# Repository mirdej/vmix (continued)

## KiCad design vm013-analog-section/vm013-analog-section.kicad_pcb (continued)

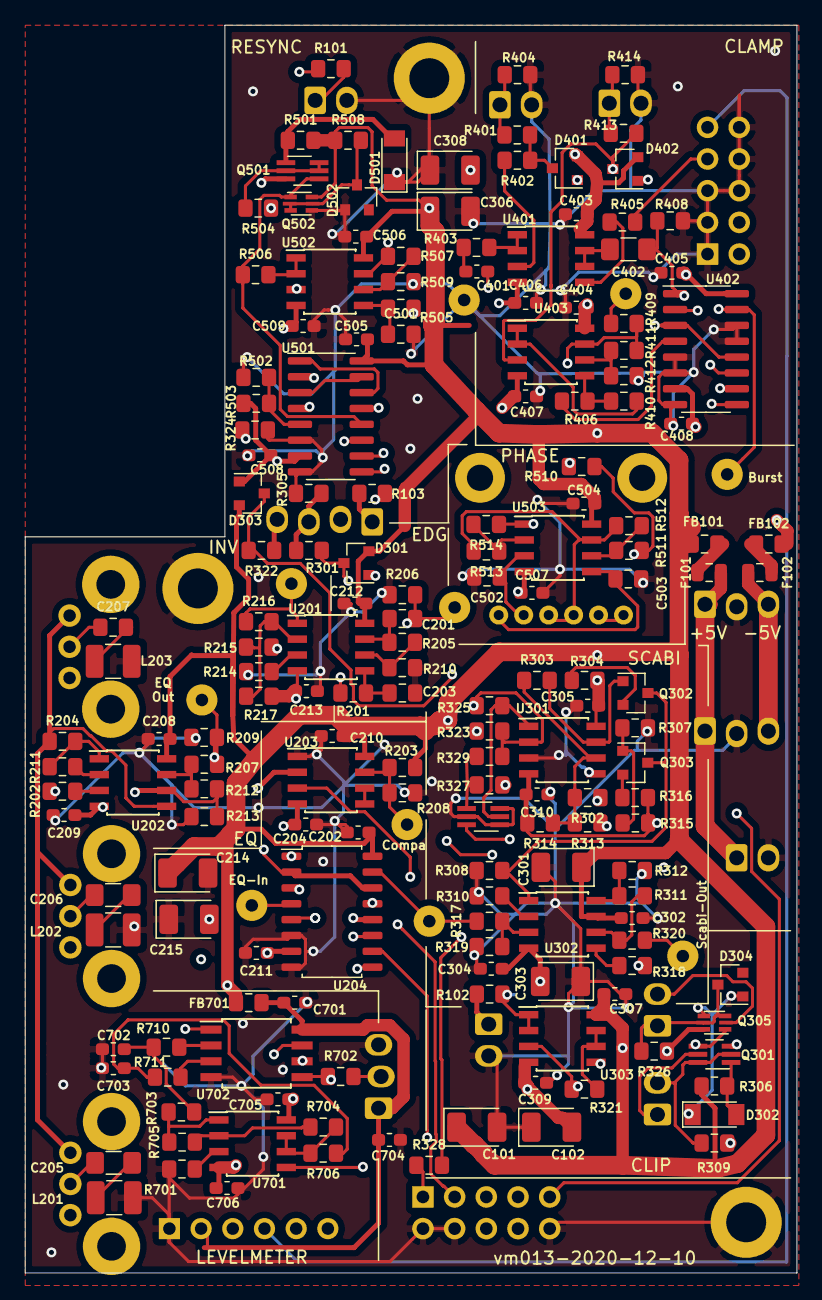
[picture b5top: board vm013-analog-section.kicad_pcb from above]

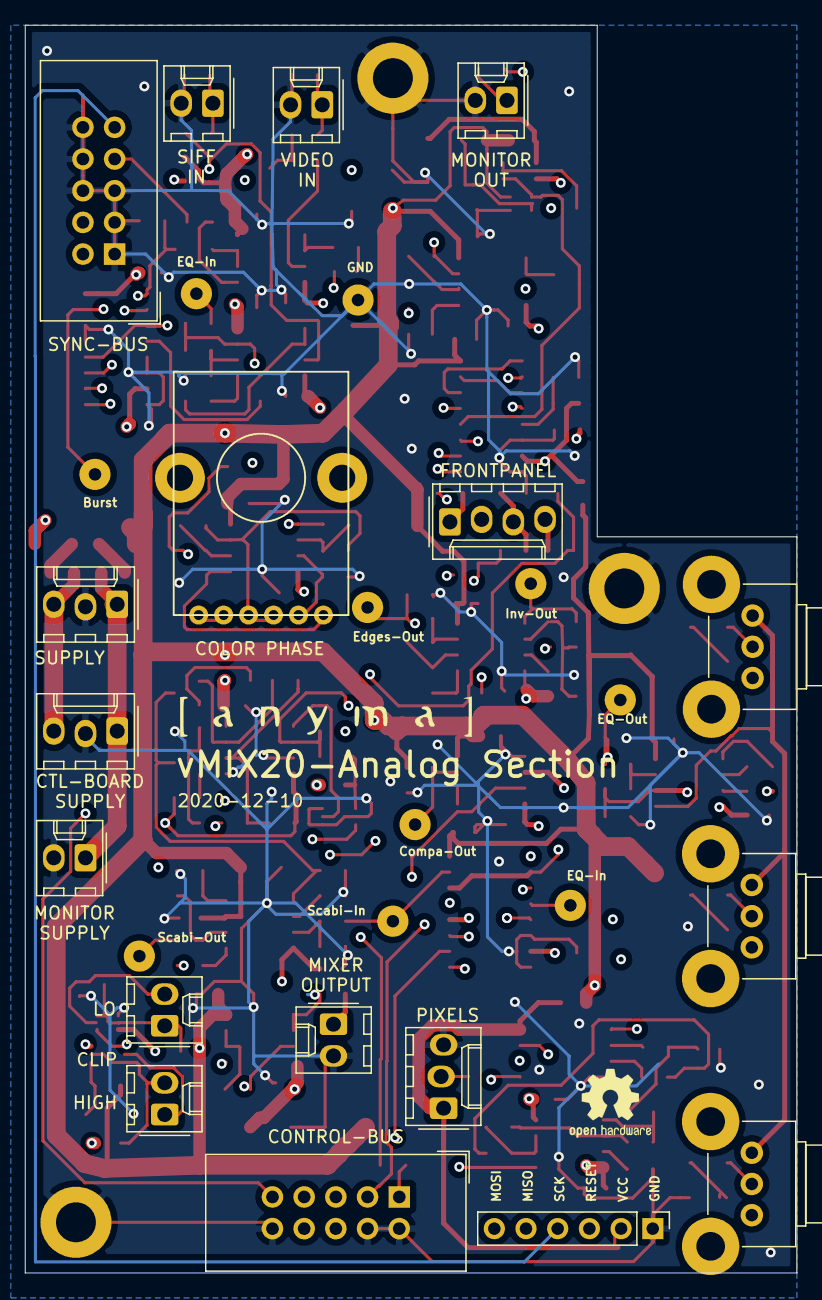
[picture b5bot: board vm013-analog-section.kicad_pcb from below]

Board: 4 copper layers, 61.8 x 100.0 mm, 205 parts (20 on the bottom side), 124 nets.

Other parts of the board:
H601, H602, H603: MountingHole_Pad; MountingHole_3.2mm_M3_ISO7380_Pad
U601: LOGO; logo_anyma
U602: LOGO; OSHW-Logo2_7.3x6mm_SilkScreen

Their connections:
GND: H601.1, H602.1, H603.1; also elsewhere on the board

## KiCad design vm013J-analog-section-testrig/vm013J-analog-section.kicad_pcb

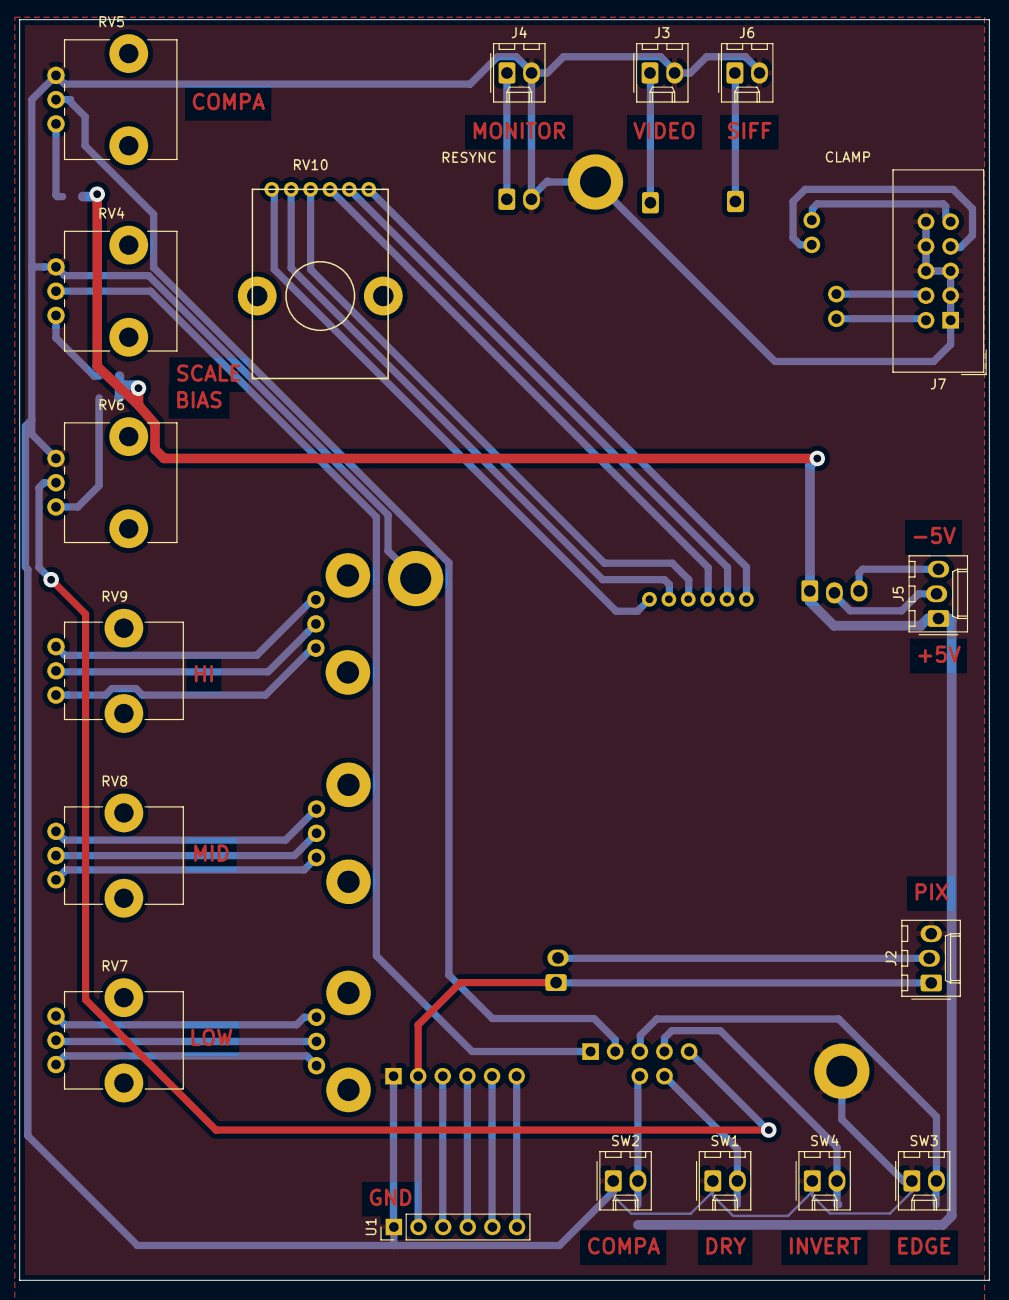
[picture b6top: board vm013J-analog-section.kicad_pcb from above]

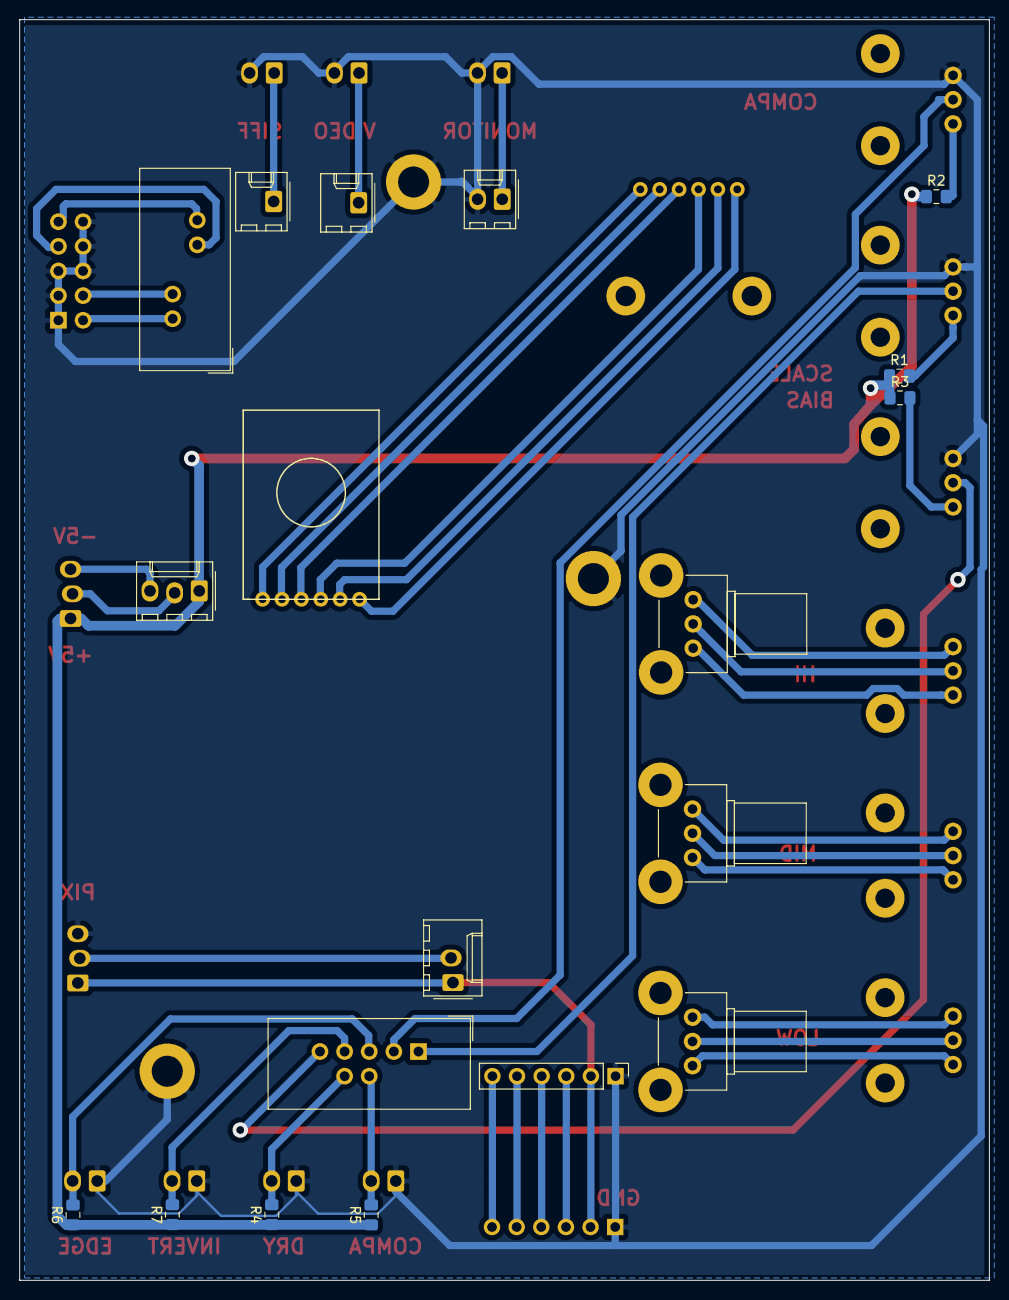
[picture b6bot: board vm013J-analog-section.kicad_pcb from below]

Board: 4 copper layers, 100.0 x 130.0 mm, 40 parts (19 on the bottom side), 42 nets.

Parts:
H601, H602, H603: MountingHole_Pad; MountingHole_3.2mm_M3_ISO7380_Pad
J1, J2: pixels; Molex_KK-254_AE-6410-03A_1x03_P2.54mm_Vertical
J3, J103: COMPOSITE-INPUT; Molex_KK-254_AE-6410-02A_1x02_P2.54mm_Vertical
J4, J104: MONITOR_OUT; Molex_KK-254_AE-6410-02A_1x02_P2.54mm_Vertical
J5, J105: Power; Molex_KK-254_AE-6410-03A_1x03_P2.54mm_Vertical
J6, J106: SIFF-INPUT; Molex_KK-254_AE-6410-02A_1x02_P2.54mm_Vertical
J7, J110: SYNC-BUS; IDC-Header_2x05_P2.54mm_Vertical
J107: FROM CTL; IDC-Header_2x05_P2.54mm_Vertical
R1, R2, R3: 40k; R_0805_2012Metric_Pad1.15x1.40mm_HandSolder
R4, R5, R6, R7: 4k7; R_0805_2012Metric_Pad1.15x1.40mm_HandSolder
RV1, RV2, RV3: R_POT; Potentiometer_Alps_RK09K_Single_Horizontal
RV4, RV5, RV6: R_POT; Potentiometer_Alps_RK09L_Single_Vertical
RV7, RV8, RV9: R_POT; Potentiometer_Alps_RK09K_Single_Vertical
RV10, RV501: R_POT_Dual; RK12L123
SW1, SW2, SW3, SW4: SW_Push; Molex_KK-254_AE-6410-02A_1x02_P2.54mm_Vertical
U1, U7: AnymaISP; PinHeader_1x06_P2.54mm_Vertical

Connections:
+5V: J5.1, J105.1, R1.1, R2.1, R3.1, R4.1, R5.1, R6.1, R7.1
/Levelmeter/miso: U1.5, U7.5
/Levelmeter/mosi: U1.6, U7.6
/Levelmeter/reset: U1.3, U7.3
/Levelmeter/sck: U1.4, U7.4
GND: H601.1, H602.1, H603.1, J2.3, J3.2, J4.2, J6.2, J7.1, J7.3, J7.5, J7.6, J7.8, J7.10, J104.2, RV4.3, RV5.3, RV6.3, SW1.1, SW2.1, SW3.1, SW4.1, U1.1, U7.1
unnamed: J1.2, J2.2
unnamed: J3.1, J103.1
unnamed: J4.1, J104.1
unnamed: J5.2, J105.2
unnamed: J5.3, J105.3
unnamed: J6.1, J106.1
unnamed: R1.2, RV4.1
unnamed: R2.2, RV5.1
unnamed: R3.2, RV6.1
unnamed: RV1.1, RV7.1
unnamed: RV1.2, RV7.2
unnamed: RV1.3, RV7.3
unnamed: RV2.1, RV8.1
unnamed: RV2.2, RV8.2
unnamed: RV2.3, RV8.3
unnamed: RV3.1, RV9.1
unnamed: RV3.2, RV9.2
unnamed: RV3.3, RV9.3
unnamed: RV10.1, RV501.1
unnamed: RV10.2, RV501.2
unnamed: RV10.3, RV501.3
unnamed: RV10.4, RV501.4
unnamed: RV10.5, RV501.5
unnamed: RV10.6, RV501.6
VCC: J1.1, J2.1, U1.2, U7.2
bias_cv: J107.9, RV6.2
compa_bypass: J107.6, R5.2, SW2.2
compa_cv: J107.3, RV5.2
drywet: J107.8, R4.2, SW1.2
edges_bypass: J107.5, R6.2, SW3.2
genlock: J7.7, J110.7
hsync: J7.2, J110.2
inverter_bypass: J107.7, R7.2, SW4.2
porch: J7.4, J110.4
scale_cv: J107.1, RV4.2
vsync: J7.9, J110.9

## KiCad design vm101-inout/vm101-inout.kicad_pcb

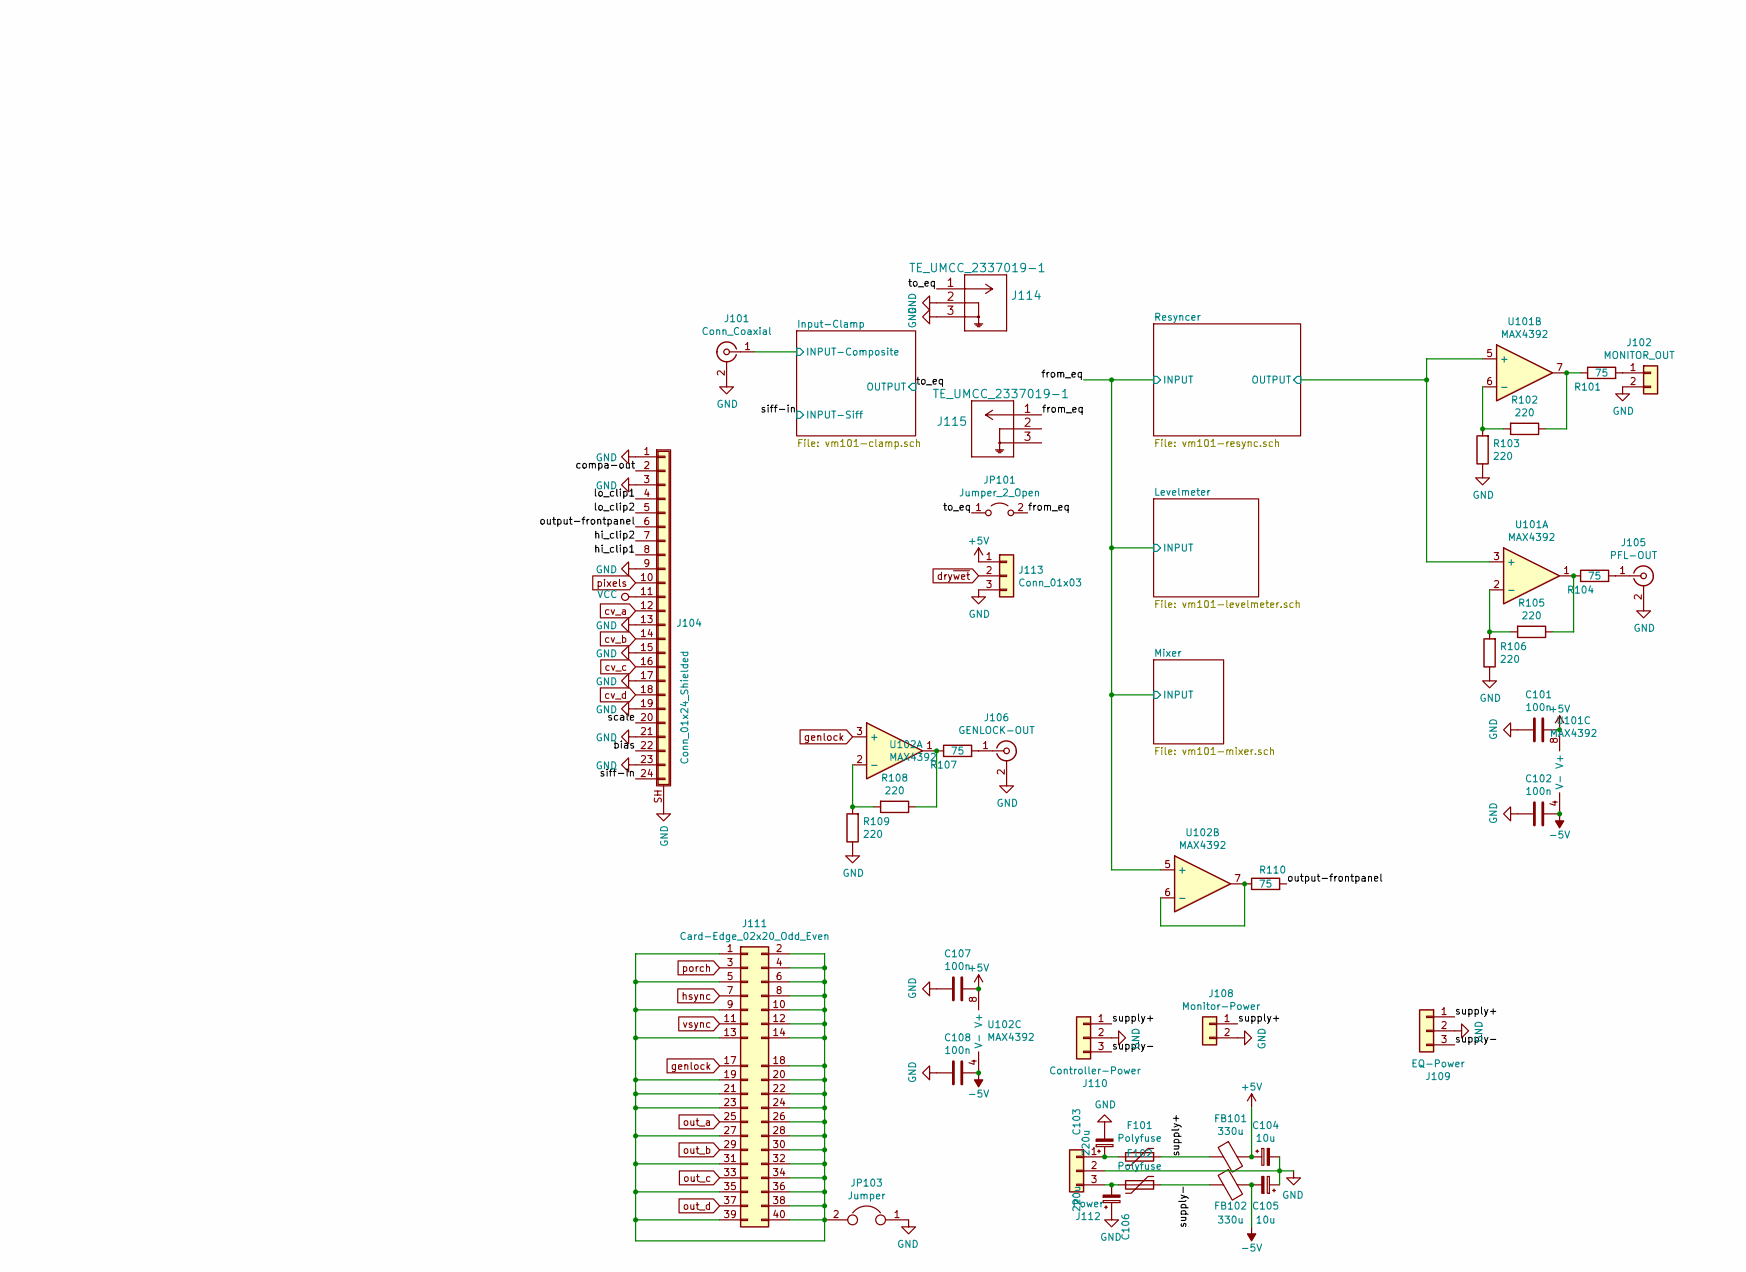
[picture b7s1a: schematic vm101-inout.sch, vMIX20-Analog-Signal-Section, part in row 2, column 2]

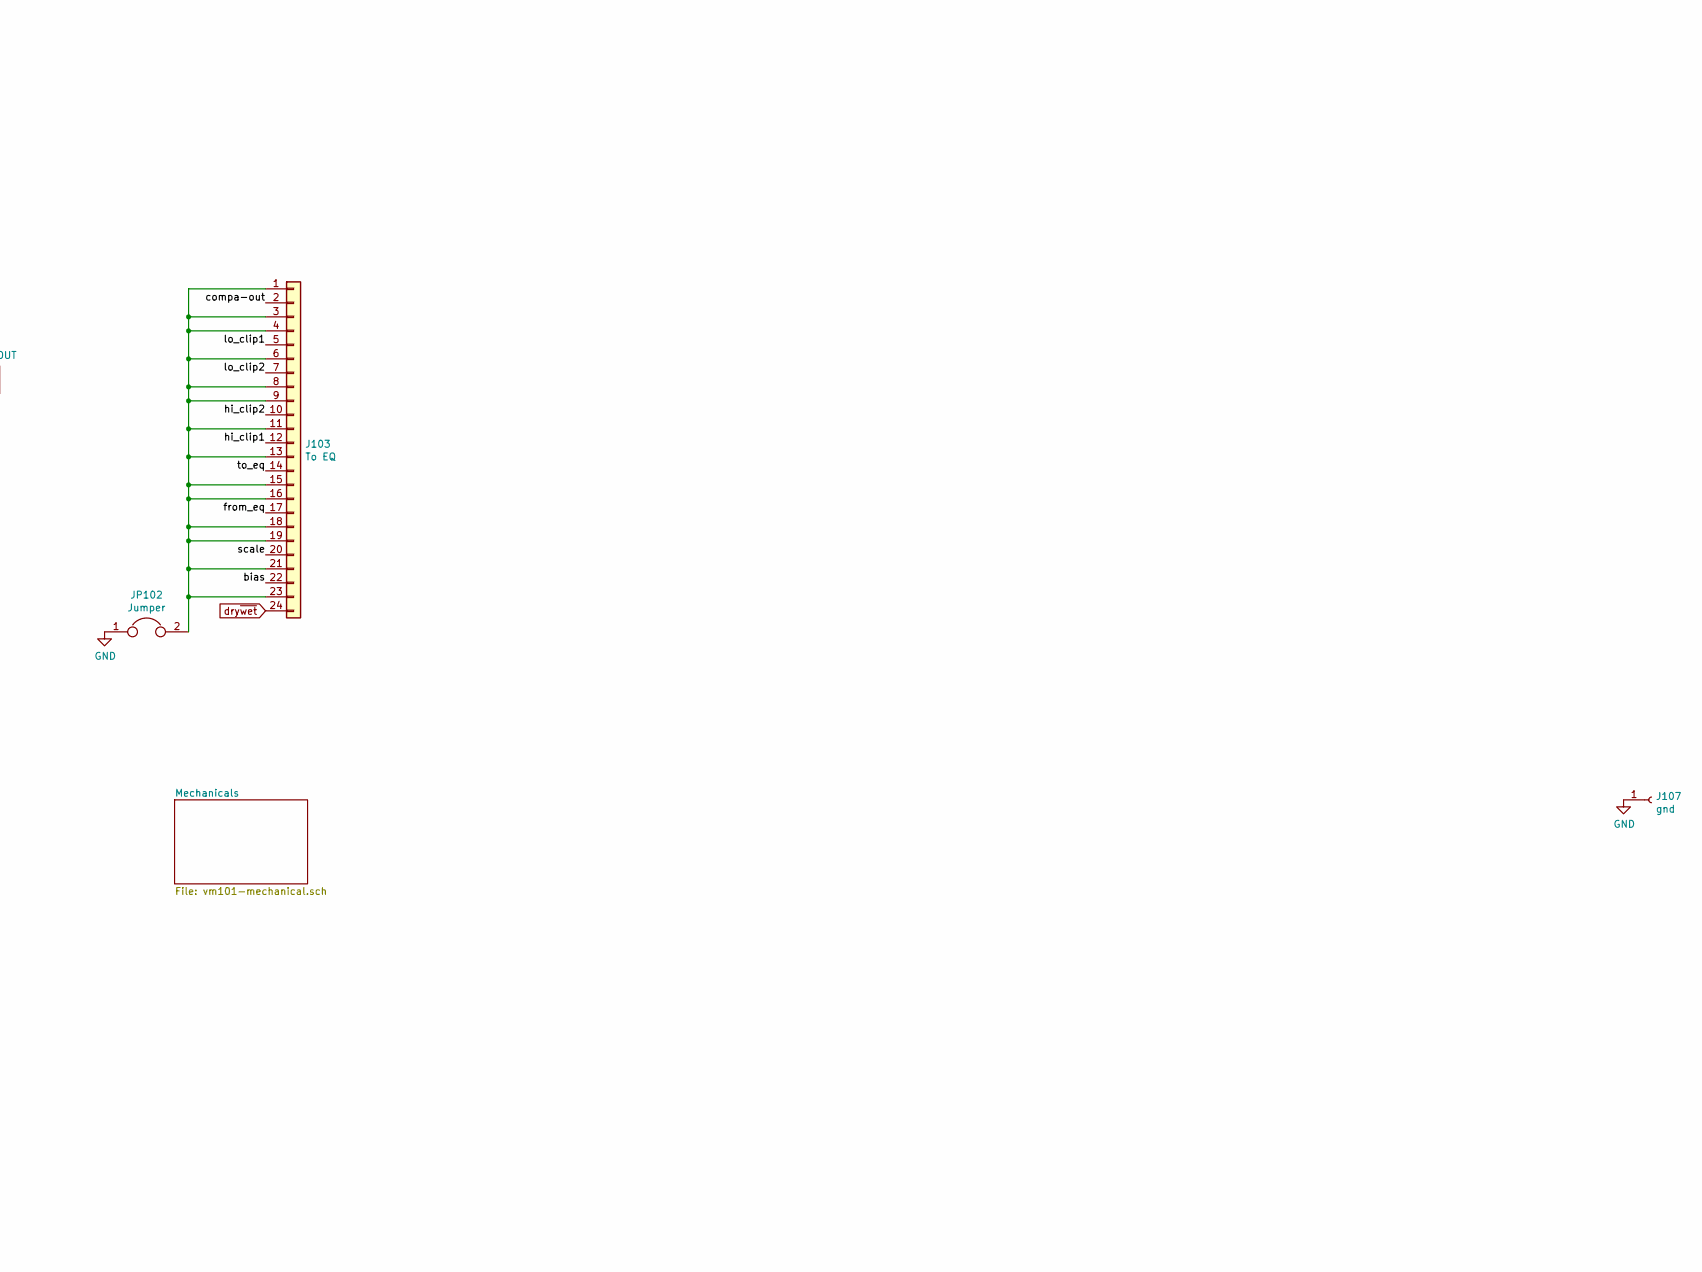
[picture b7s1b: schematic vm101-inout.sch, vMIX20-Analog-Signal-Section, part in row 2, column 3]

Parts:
C101, C102, C107, C108: 100n; C_0603_1608Metric_Pad1.05x0.95mm_HandSolder
C103, C106: 220u; CP_Elec_10x10.5
C104, C105: 10u; CP_EIA-3528-21_Kemet-B_Pad1.50x2.35mm_HandSolder
F101, F102: Polyfuse; Fuse_0805_2012Metric
FB101, FB102: 330u; L_0805_2012Metric_Pad1.15x1.40mm_HandSolder
J101: Conn_Coaxial; BNC_Amphenol_B6252HB-NPP3G-50_Horizontal
J102: MONITOR_OUT; Molex_KK-254_AE-6410-02A_1x02_P2.54mm_Vertical
J103: To EQ; Hirose_FH12-24S-0.5SH_1x24-1MP_P0.50mm_Horizontal
J104: Conn_01x24_Shielded; Hirose_FH12-24S-0.5SH_1x24-1MP_P0.50mm_Horizontal
J105: PFL-OUT; BNC_Amphenol_B6252HB-NPP3G-50_Horizontal
J106: GENLOCK-OUT; BNC_Amphenol_B6252HB-NPP3G-50_Horizontal
J107: gnd; Solderpad_1mm
J108: Monitor-Power; Molex_KK-254_AE-6410-02A_1x02_P2.54mm_Vertical
J109: EQ-Power; Molex_KK-254_AE-6410-03A_1x03_P2.54mm_Vertical
J110: Controller-Power; Molex_KK-254_AE-6410-03A_1x03_P2.54mm_Vertical
J111: Card-Edge_02x20_Odd_Even; Samtec_MECF-20-0_-L-DV_2x20_P1.27mm_Polarized_Edge
J112: Power; Molex_KK-254_AE-6410-03A_1x03_P2.54mm_Vertical
J113: Conn_01x03; PinHeader_1x03_P2.54mm_Vertical
J114, J115: TE_UMCC_2337019-1
JP101: Jumper_2_Open; PinHeader_1x02_P2.54mm_Vertical
JP102: Jumper; SolderJumper-2_P1.3mm_Bridged_Pad1.0x1.5mm
JP103: Jumper; SolderJumper-2_P1.3mm_Open_TrianglePad1.0x1.5mm
R101, R104, R107, R110: 75; R_0805_2012Metric_Pad1.15x1.40mm_HandSolder
R102, R103, R105, R106, R108, R109: 220; R_0805_2012Metric_Pad1.15x1.40mm_HandSolder
U101, U102: MAX4392; SOIC-8_3.9x4.9mm_P1.27mm

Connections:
+5V: C101.2, C104.1, C107.2, FB101.2, J113.1, U101.8 (V+), U102.8 (V+); also elsewhere on the board
-5V: C102.2, C105.2, C108.2, FB102.2, U101.4 (V-), U102.4 (V-); also elsewhere on the board
/Input-Clamp/INPUT-Composite: J101.1 (In); also elsewhere on the board
/Resyncer/OUTPUT: U101.3 (+), U101.5 (+); also elsewhere on the board
/bias: J103.22, J104.22
/compa-out: J103.2, J104.2
/from_eq: J103.17, J115.1, JP101.2 (B), U102.5 (+); also elsewhere on the board
/hi_clip1: J103.12, J104.8
/hi_clip2: J103.10, J104.7
/lo_clip1: J103.5, J104.4
/lo_clip2: J103.7, J104.5
/output-frontpanel: J104.6, R110.2
/scale: J103.20, J104.20
/siff-in: J104.24; also elsewhere on the board
/supply+: F101.1, FB101.1, J108.1, J109.1, J110.1
/supply-: F102.1, FB102.1, J109.3, J110.3
/to_eq: J103.14, J114.1, JP101.1 (A); also elsewhere on the board
GND: C101.1, C102.1, C103.2, C104.2, C105.1, C106.1, C107.1, C108.1, J101.2 (Ext), J102.2, J104.1, J104.3, J104.9, J104.13, J104.15, J104.17, J104.19, J104.21, J104.23, J104.SH (Shield), J105.2 (Ext), J106.2 (Ext), J107.1, J108.2, J109.2, J110.2, J112.2, J113.3, J114.2, J114.3, JP102.1, JP103.1, R103.1, R106.1, R109.1; also elsewhere on the board
unnamed: C103.1, F101.2, J112.1
unnamed: C106.2, F102.2, J112.3
unnamed: J102.1, R101.2
unnamed: J103.1, J103.3, J103.4, J103.6, J103.8, J103.9, J103.11, J103.13, J103.15, J103.16, J103.18, J103.19, J103.21, J103.23, JP102.2
unnamed: J105.1 (In), R104.2
unnamed: J106.1 (In), R107.2
unnamed: J111.1, J111.2, J111.4, J111.5, J111.6, J111.8, J111.9, J111.10, J111.12, J111.13, J111.14, J111.18, J111.19, J111.20, J111.21, J111.22, J111.23, J111.24, J111.26, J111.27, J111.28, J111.30, J111.31, J111.32, J111.34, J111.35, J111.36, J111.38, J111.39, J111.40, JP103.2
unnamed: R101.1, R102.1, U101.7
unnamed: R102.2, R103.2, U101.6 (-)
unnamed: R104.1, R105.1, U101.1
unnamed: R105.2, R106.2, U101.2 (-)
unnamed: R107.1, R108.1, U102.1
unnamed: R108.2, R109.2, U102.2 (-)
unnamed: R110.1, U102.6 (-), U102.7
VCC: J104.11; also elsewhere on the board
cv_a: J104.12; also elsewhere on the board
cv_b: J104.14; also elsewhere on the board
cv_c: J104.16; also elsewhere on the board
cv_d: J104.18; also elsewhere on the board
dry~wet~: J103.24, J113.2; also elsewhere on the board
genlock: J111.17, U102.3 (+); also elsewhere on the board
hsync: J111.7; also elsewhere on the board
out_a: J111.25; also elsewhere on the board
out_b: J111.29; also elsewhere on the board
out_c: J111.33; also elsewhere on the board
out_d: J111.37; also elsewhere on the board
pixels: J104.10; also elsewhere on the board
porch: J111.3; also elsewhere on the board
vsync: J111.11; also elsewhere on the board

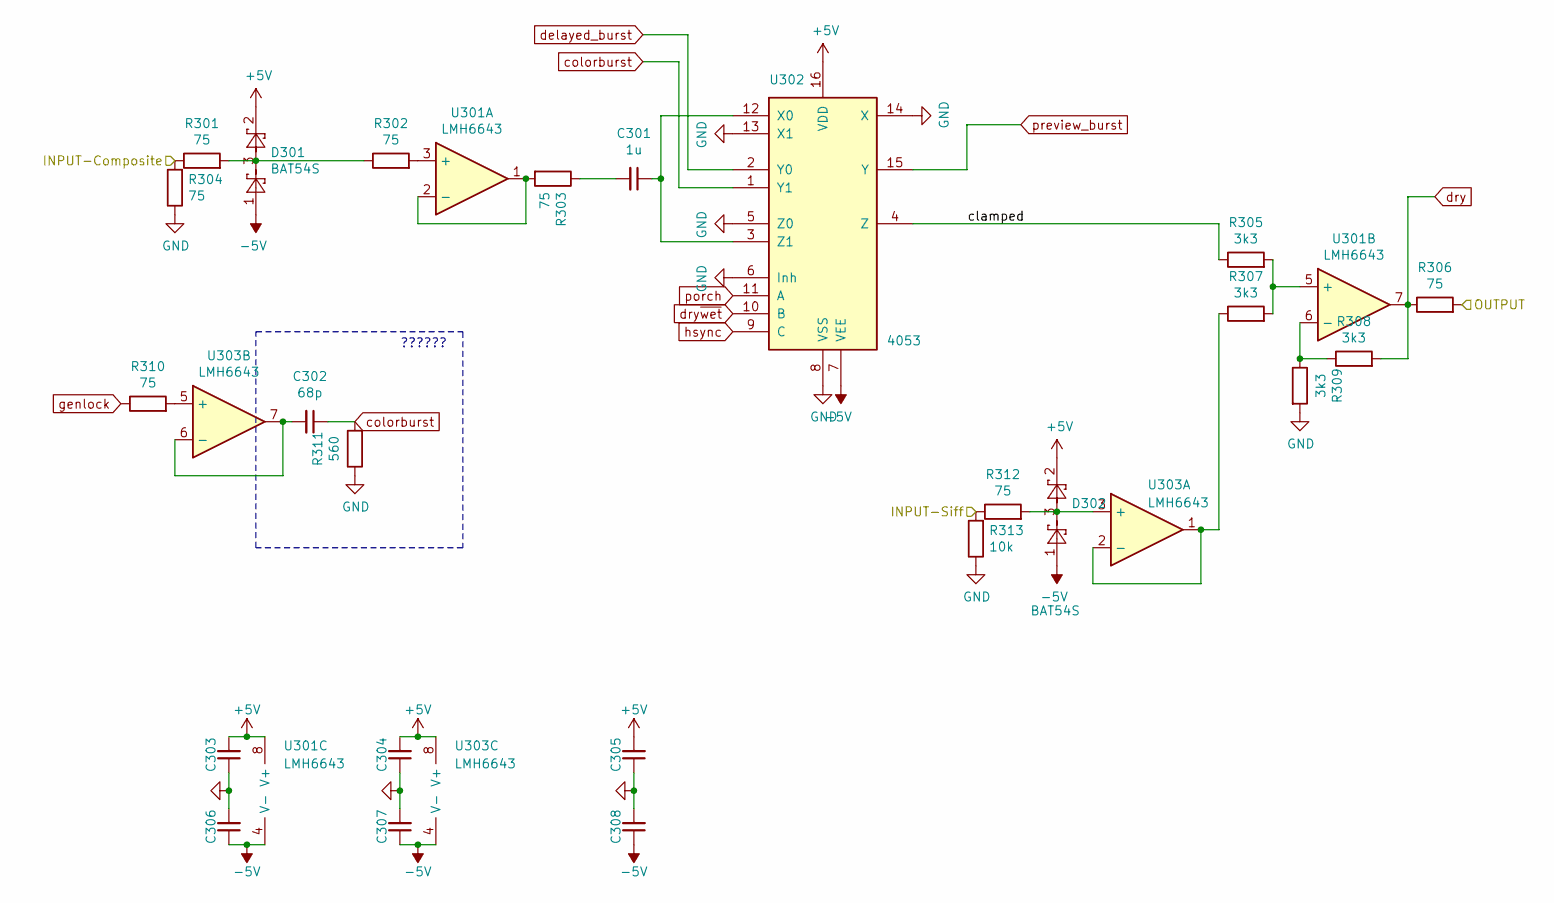
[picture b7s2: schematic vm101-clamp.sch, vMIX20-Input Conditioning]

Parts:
C301: 1u; C_0603_1608Metric_Pad1.05x0.95mm_HandSolder
C302: 68p; C_1206_3216Metric_Pad1.42x1.75mm_HandSolder
C303, C304, C305, C306, C307, C308: 100n; C_0603_1608Metric_Pad1.05x0.95mm_HandSolder
D301, D302: BAT54S; SOT-23
R301, R302, R303, R304, R306, R310, R312: 75; R_0805_2012Metric_Pad1.15x1.40mm_HandSolder
R305, R307, R308, R309: 3k3; R_0805_2012Metric_Pad1.15x1.40mm_HandSolder
R311: 560; R_0805_2012Metric_Pad1.15x1.40mm_HandSolder
R313: 10k; R_0805_2012Metric_Pad1.15x1.40mm_HandSolder
U301, U303: LMH6643; SOIC-8_3.9x4.9mm_P1.27mm
U302: 4053; SOIC-16_3.9x9.9mm_P1.27mm

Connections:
+5V: C303.2, C304.2, C305.2, D301.2, D302.2, U301.8 (V+), U302.16 (VDD), U303.8 (V+); also elsewhere on the board
-5V: C306.1, C307.1, C308.1, D301.1, D302.1, U301.4 (V-), U302.7 (VEE), U303.4 (V-); also elsewhere on the board
/Input-Clamp/INPUT-Composite: R301.1, R304.2; also elsewhere on the board
/Input-Clamp/clamped: R305.1, U302.4 (Z)
/siff-in: R312.1, R313.2; also elsewhere on the board
/to_eq: R306.2; also elsewhere on the board
GND: C303.1, C304.1, C305.1, C306.2, C307.2, C308.2, R304.1, R309.2, R311.1, R313.1, U302.5 (Z0), U302.6 (Inh), U302.8 (VSS), U302.13 (X1), U302.14 (X); also elsewhere on the board
unnamed: C301.1, U302.3 (Z1), U302.12 (X0)
unnamed: C301.2, R303.1
unnamed: C302.2, U303.6 (-), U303.7
unnamed: D301.3, R301.2, R302.1
unnamed: D302.3, R312.2, U303.3 (+)
unnamed: R302.2, U301.3 (+)
unnamed: R303.2, U301.1, U301.2 (-)
unnamed: R305.2, R307.2, U301.5 (+)
unnamed: R307.1, U303.1, U303.2 (-)
unnamed: R308.1, R309.1, U301.6 (-)
unnamed: R310.2, U303.5 (+)
colorburst: C302.1, R311.2, U302.1 (Y1); also elsewhere on the board
delayed_burst: U302.2 (Y0); also elsewhere on the board
dry: R306.1, R308.2, U301.7; also elsewhere on the board
dry~wet~: U302.10 (B); also elsewhere on the board
genlock: R310.1; also elsewhere on the board
hsync: U302.9 (C); also elsewhere on the board
porch: U302.11 (A); also elsewhere on the board
preview_burst: U302.15 (Y); also elsewhere on the board

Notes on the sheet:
??????

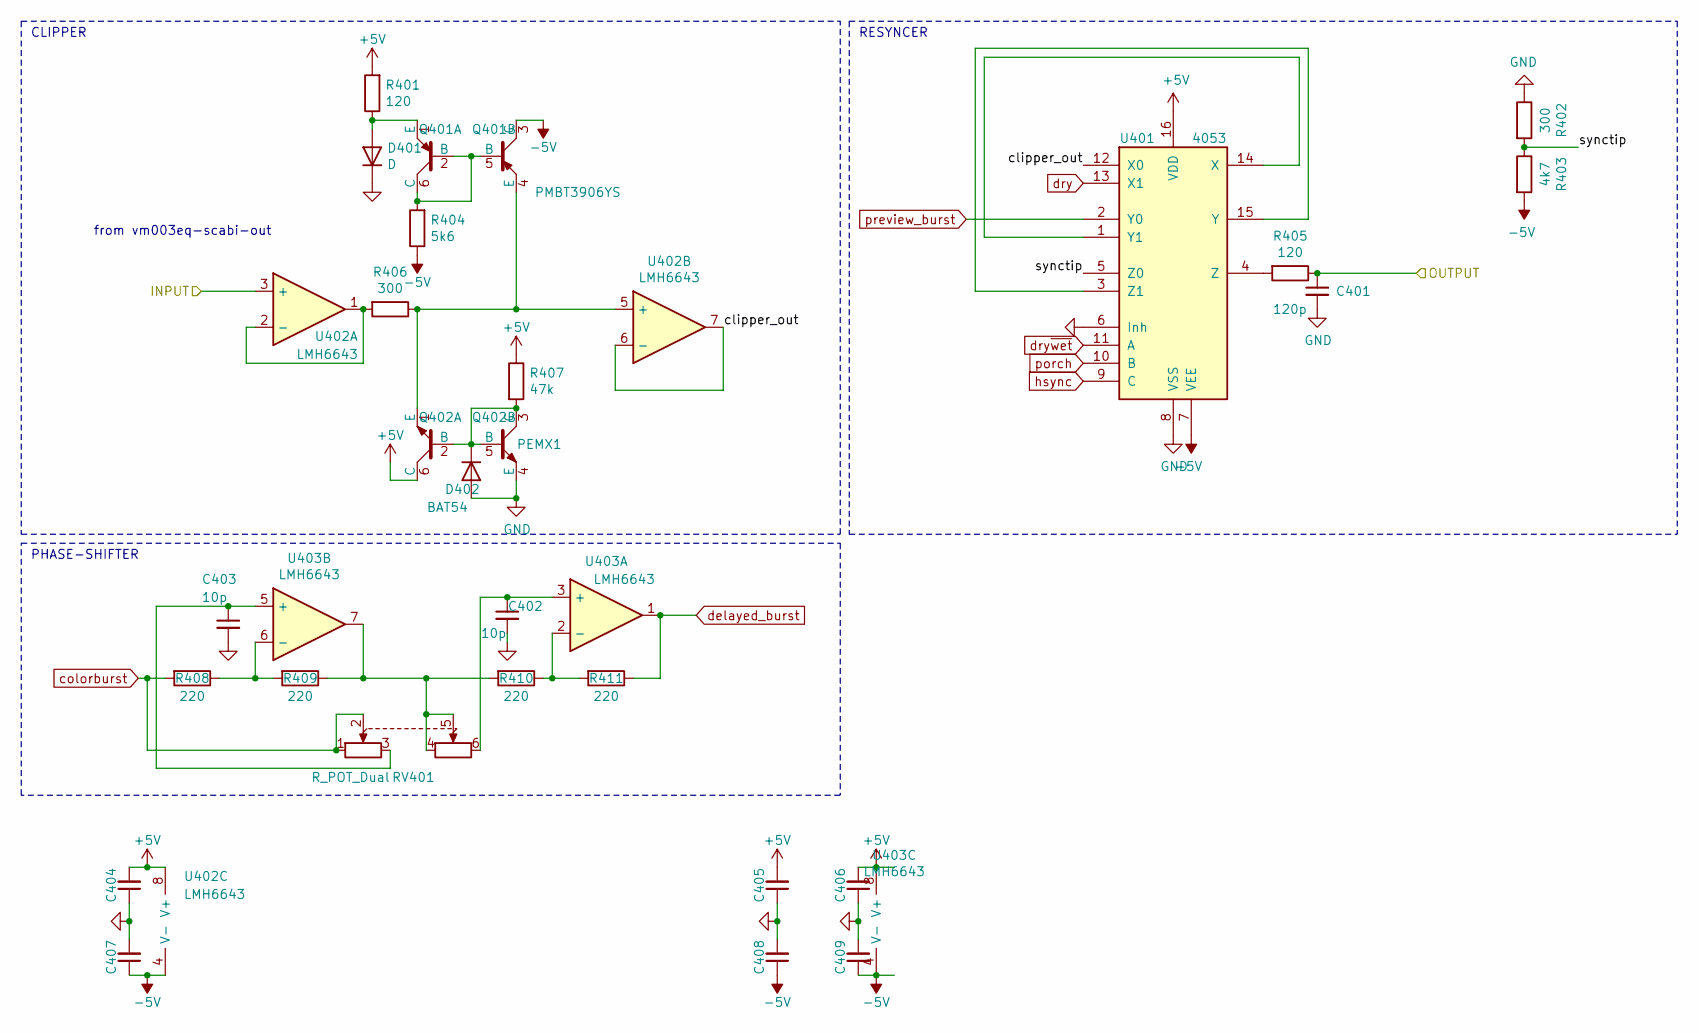
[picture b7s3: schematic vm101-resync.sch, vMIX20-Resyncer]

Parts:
C401: 120p; C_0805_2012Metric_Pad1.15x1.40mm_HandSolder
C402, C403: 10p; C_0805_2012Metric_Pad1.15x1.40mm_HandSolder
C404, C405, C406, C407, C408, C409: 100n; C_0603_1608Metric_Pad1.05x0.95mm_HandSolder
D401: D; D_MiniMELF
D402: BAT54; D_SOT-23_ANK
Q401: PMBT3906YS; SOT-363_SC-70-6_Handsoldering
Q402: PEMX1; SOT-666
R401, R405: 120; R_0805_2012Metric_Pad1.15x1.40mm_HandSolder
R402, R406: 300; R_0805_2012Metric_Pad1.15x1.40mm_HandSolder
R403: 4k7; R_0805_2012Metric_Pad1.15x1.40mm_HandSolder
R404: 5k6; R_0805_2012Metric_Pad1.15x1.40mm_HandSolder
R407: 47k; R_0805_2012Metric_Pad1.15x1.40mm_HandSolder
R408, R409, R410, R411: 220; R_0805_2012Metric_Pad1.15x1.40mm_HandSolder
RV401: R_POT_Dual; RK12L123
U401: 4053; SOIC-16_3.9x9.9mm_P1.27mm
U402, U403: LMH6643; SOIC-8_3.9x4.9mm_P1.27mm

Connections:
+5V: C404.2, C405.2, C406.2, Q402.6 (C), R401.2, R407.1, U401.16 (VDD), U402.8 (V+), U403.8 (V+); also elsewhere on the board
-5V: C407.1, C408.1, C409.1, Q401.3 (C), R403.2, R404.1, U401.7 (VEE), U402.4 (V-), U403.4 (V-); also elsewhere on the board
/Resyncer/OUTPUT: C401.1, R405.1; also elsewhere on the board
/Resyncer/clipper_out: U401.12 (X0), U402.6 (-), U402.7
/Resyncer/synctip: R402.2, R403.1, U401.5 (Z0)
/from_eq: U402.3 (+); also elsewhere on the board
GND: C401.2, C402.2, C403.2, C404.1, C405.1, C406.1, C407.2, C408.2, C409.2, D401.1 (K), D402.2 (A), Q402.4 (E), R402.1, RV401.7, RV401.9, U401.6 (Inh), U401.8 (VSS); also elsewhere on the board
unnamed: C402.1, RV401.6, U403.3 (+)
unnamed: C403.1, RV401.3, U403.5 (+)
unnamed: D401.2 (A), Q401.1 (E), R401.1
unnamed: D402.1 (K), Q402.2 (B), Q402.3 (C), Q402.5 (B), R407.2
unnamed: Q401.2 (B), Q401.5 (B), Q401.6 (C), R404.2
unnamed: Q401.4 (E), Q402.1 (E), R406.1, U402.5 (+)
unnamed: R405.2, U401.4 (Z)
unnamed: R406.2, U402.1, U402.2 (-)
unnamed: R408.1, R409.2, U403.6 (-)
unnamed: R409.1, R410.2, RV401.4, RV401.5, U403.7
unnamed: R410.1, R411.2, U403.2 (-)
unnamed: U401.1 (Y1), U401.14 (X)
unnamed: U401.3 (Z1), U401.15 (Y)
colorburst: R408.2, RV401.1, RV401.2; also elsewhere on the board
delayed_burst: R411.1, U403.1; also elsewhere on the board
dry: U401.13 (X1); also elsewhere on the board
dry~wet~: U401.11 (A); also elsewhere on the board
hsync: U401.9 (C); also elsewhere on the board
porch: U401.10 (B); also elsewhere on the board
preview_burst: U401.2 (Y0); also elsewhere on the board

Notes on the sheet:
PHASE-SHIFTER
CLIPPER
RESYNCER
from vm003eq-scabi-out

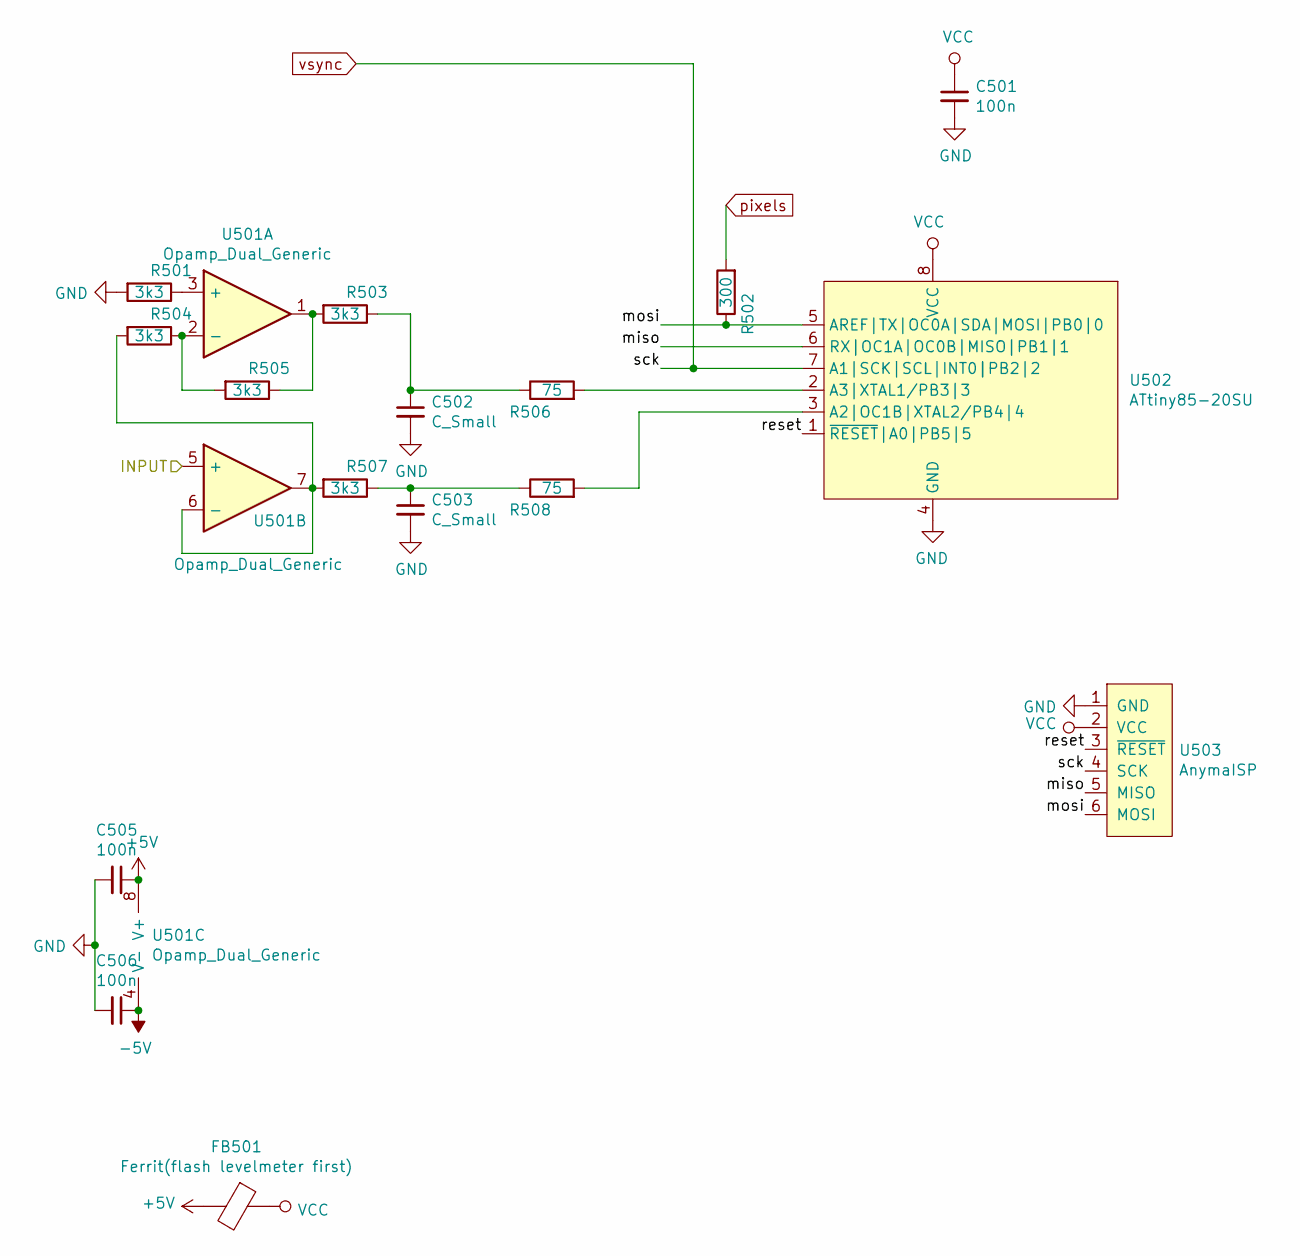
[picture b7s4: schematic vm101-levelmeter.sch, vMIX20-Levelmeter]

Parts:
C501, C505, C506: 100n; C_0603_1608Metric_Pad1.05x0.95mm_HandSolder
C502, C503: C_Small; C_0603_1608Metric_Pad1.05x0.95mm_HandSolder
FB501: Ferrit(flash levelmeter first); L_0805_2012Metric_Pad1.15x1.40mm_HandSolder
R501, R503, R504, R505, R507: 3k3; R_0805_2012Metric_Pad1.15x1.40mm_HandSolder
R502: 300; R_0805_2012Metric_Pad1.15x1.40mm_HandSolder
R506, R508: 75; R_0805_2012Metric_Pad1.15x1.40mm_HandSolder
U501: Opamp_Dual_Generic; SOIC-8_3.9x4.9mm_P1.27mm
U502: ATtiny85-20SU; SOIJ-8_5.3x5.3mm_P1.27mm
U503: AnymaISP; Pinhead_SMD_6

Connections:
+5V: C505.1, FB501.2, U501.8 (V+); also elsewhere on the board
-5V: C506.1, U501.4 (V-); also elsewhere on the board
/Levelmeter/miso: U502.6 (RX|OC1A|OC0B|MISO|PB1|1), U503.5 (MISO)
/Levelmeter/mosi: R502.1, U502.5 (AREF|TX|OC0A|SDA|MOSI|PB0|0), U503.6 (MOSI)
/Levelmeter/reset: U502.1 (~RESET~|A0|PB5|5), U503.3 (~RESET)
/from_eq: U501.5 (+); also elsewhere on the board
GND: C501.2, C502.2, C503.2, C505.2, C506.2, R501.2, U502.4 (GND), U503.1 (GND); also elsewhere on the board
unnamed: C502.1, R503.1, R506.1
unnamed: C503.1, R507.1, R508.1
unnamed: R501.1, U501.3 (+)
unnamed: R503.2, R505.1, U501.1
unnamed: R504.1, R505.2, U501.2 (-)
unnamed: R504.2, R507.2, U501.6 (-), U501.7
unnamed: R506.2, U502.2 (A3|XTAL1/PB3|3)
unnamed: R508.2, U502.3 (A2|OC1B|XTAL2/PB4|4)
VCC: C501.1, FB501.1, U502.8 (VCC), U503.2 (VCC); also elsewhere on the board
pixels: R502.2; also elsewhere on the board
vsync: U502.7 (A1|SCK|SCL|INT0|PB2|2), U503.4 (SCK); also elsewhere on the board

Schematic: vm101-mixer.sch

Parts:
C601, C602, C603, C604: 10u; CP_EIA-3528-21_Kemet-B_Pad1.50x2.35mm_HandSolder
FB601, FB602: 330u; L_0805_2012Metric_Pad1.15x1.40mm_HandSolder
J601: Conn_01x03; Molex_KK-254_AE-6410-03A_1x03_P2.54mm_Vertical
R601: 560; R_0805_2012Metric_Pad1.15x1.40mm_HandSolder
U601: ADR510; SOT-23
U602: MAX5741; MSOP-10_3x3mm_P0.5mm

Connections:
+5V: C601.1, C602.1, FB601.2, R601.1, U602.3 (VDD); also elsewhere on the board
-5V: C603.2, C604.2, FB602.2; also elsewhere on the board
/Mixer/dac_a: U602.7 (OUTA); also elsewhere on the board
/Mixer/dac_b: U602.8 (OUTB); also elsewhere on the board
/Mixer/dac_c: U602.9 (OUTC); also elsewhere on the board
/Mixer/dac_d: U602.10 (OUTD); also elsewhere on the board
/Mixer/dac_select: J601.1, U602.1 (~CS~)
/Mixer/mosi: J601.3, U602.5 (DIN)
/Mixer/sck: J601.2, U602.2 (SCLK)
GND: C601.2, C602.2, C603.1, C604.1, U601.2 (V-), U602.4 (GND); also elsewhere on the board
unnamed: R601.2, U601.1 (V+), U602.6 (REF)

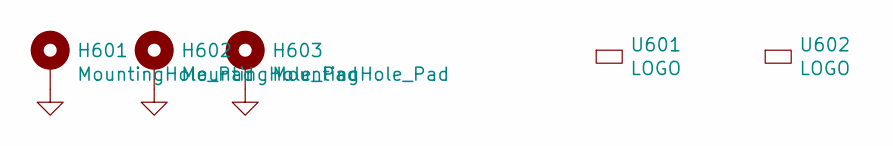
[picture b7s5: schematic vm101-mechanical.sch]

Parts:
H601, H602, H603: MountingHole_Pad; MountingHole_3.2mm_M3_ISO7380_Pad
U601: LOGO; logo_anyma
U602: LOGO; OSHW-Logo2_7.3x6mm_SilkScreen

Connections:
GND: H601.1, H602.1, H603.1; also elsewhere on the board
